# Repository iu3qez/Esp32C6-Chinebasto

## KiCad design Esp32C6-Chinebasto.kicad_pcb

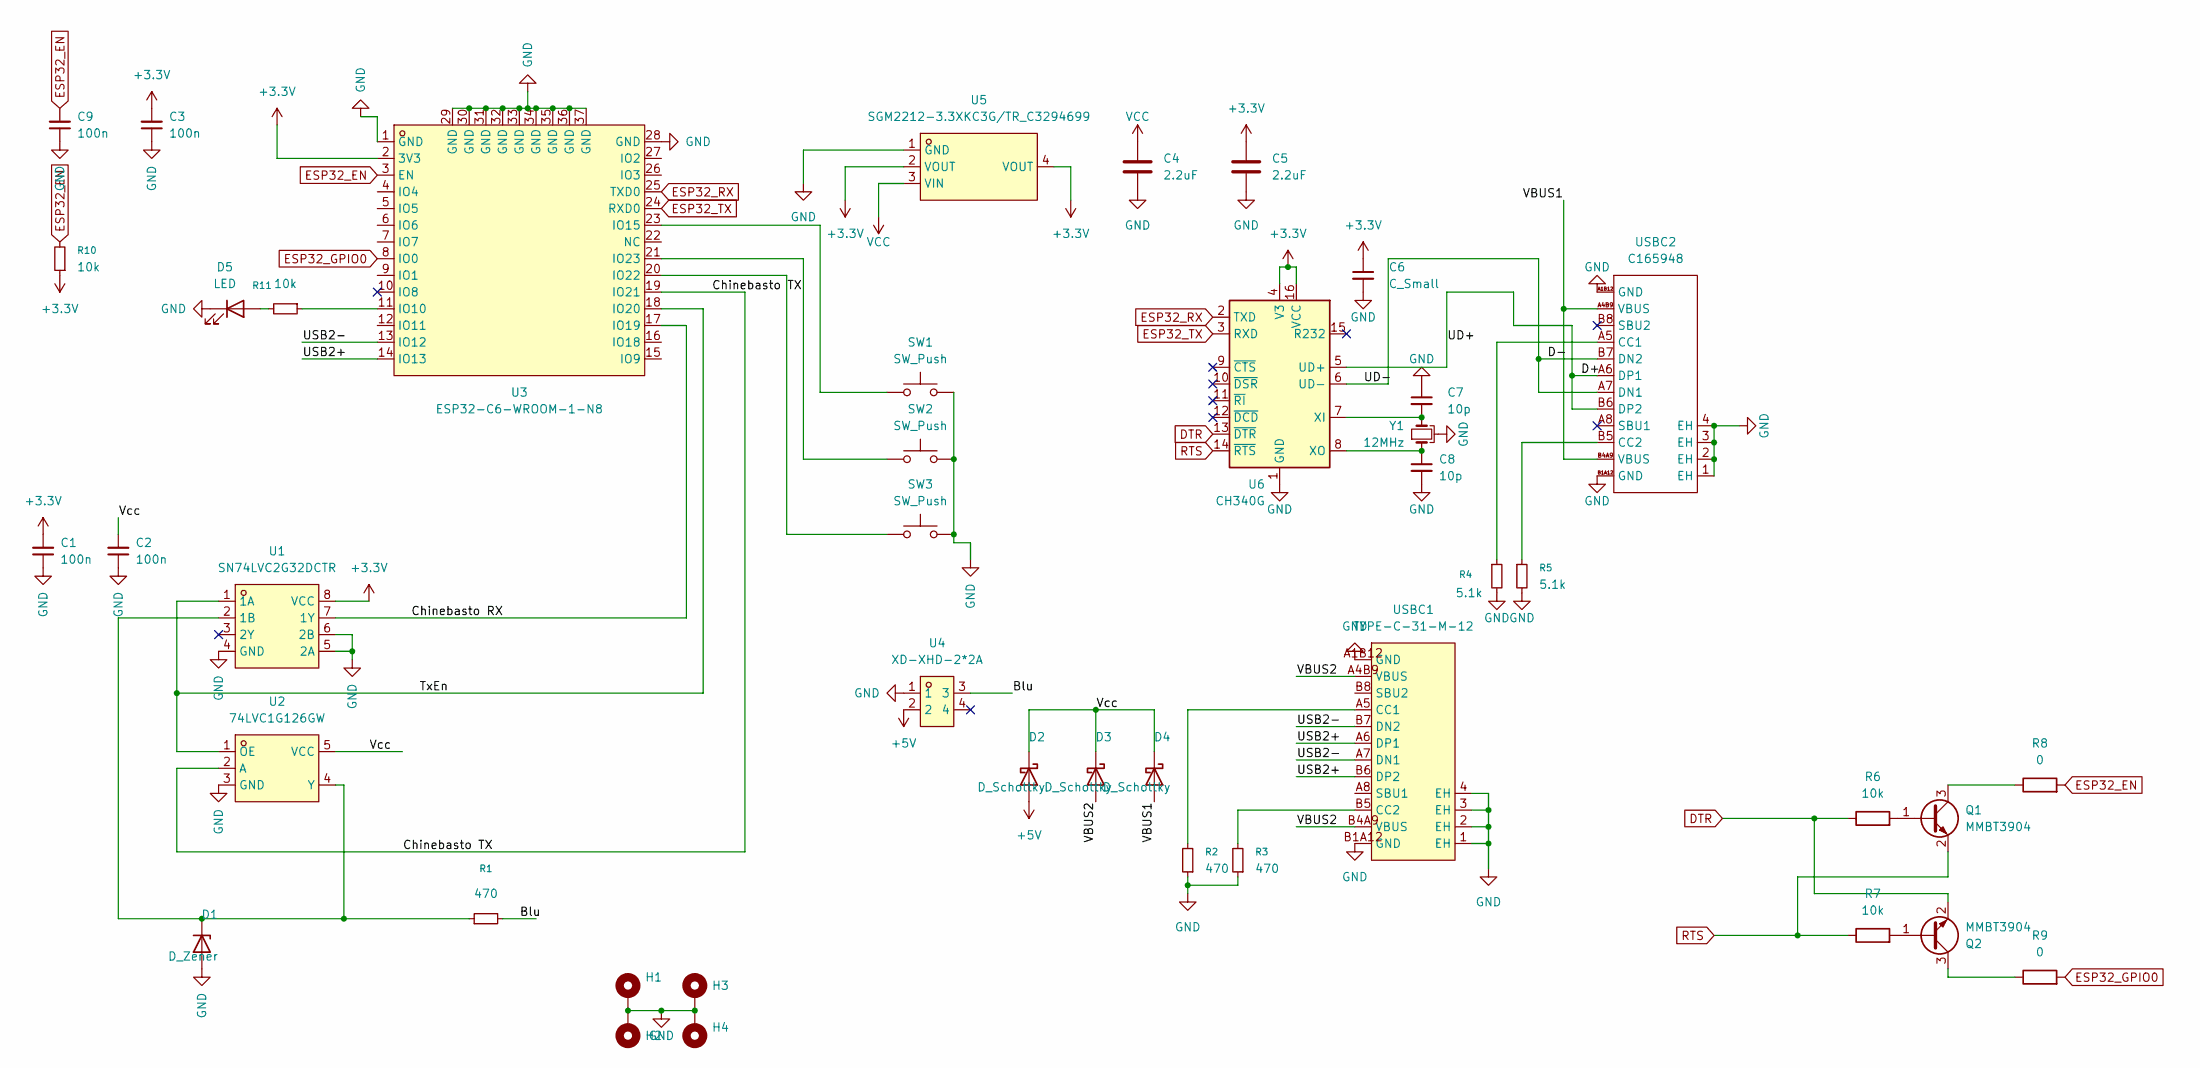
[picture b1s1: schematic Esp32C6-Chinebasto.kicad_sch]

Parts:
C1, C2, C3, C9: 100n; C_0603_1608Metric_Pad1.08x0.95mm_HandSolder
C4, C5: 2.2uF; C_0805_2012Metric_Pad1.18x1.45mm_HandSolder
C6: C_Small; C_0603_1608Metric_Pad1.08x0.95mm_HandSolder
C7, C8: 10p; C_0603_1608Metric_Pad1.08x0.95mm_HandSolder
D1: D_Zener; D_MiniMELF
D2, D3, D4: D_Schottky; D_SOD-123
D5: LED; LED_0603_1608Metric_Pad1.05x0.95mm_HandSolder
H1, H2, H3, H4: MountingHole_Pad; MountingHole_3.2mm_M3_ISO7380_Pad_TopBottom
Q1, Q2: MMBT3904; SOT-23
R1, R2, R3: 470; R_0603_1608Metric_Pad0.98x0.95mm_HandSolder
R4, R5: 5.1k; R_0603_1608Metric_Pad0.98x0.95mm_HandSolder
R6, R7, R10, R11: 10k; R_0603_1608Metric_Pad0.98x0.95mm_HandSolder
R8, R9: 0; R_0603_1608Metric_Pad0.98x0.95mm_HandSolder
SW1, SW2, SW3: SW_Push; SW_Kailh_Choc_V1V2_1.00u
U1: SN74LVC2G32DCTR; SM-8_L3.0-W2.8-P0.65-LS4.0-BL; LCSC Part C2862085
U2: 74LVC1G126GW; SOT-353-5_L2.0-W1.6-P0.65-LS2.1-BL; LCSC Part C52140429
U3: ESP32-C6-WROOM-1-N8; WIRELM-SMD_ESP32-C6-WROOM-1; LCSC Part C5366877
U4: XD-XHD-2*2A; CONN-TH_XD-XHD-2-2A; LCSC Part C17700790
U5: SGM2212-3.3XKC3G/TR_C3294699; SOT-223-3_L6.5-W3.4-P2.30-LS7.0-BR; LCSC Part C3294699
U6: CH340G; SOIC-16_L9.9-W3.9-P1.27-LS6.0-BL
USBC1: TYPE-C-31-M-12; USB-C_SMD-TYPE-C-31-M-12_1; LCSC Part C165948
USBC2: C165948; USB-C_SMD-TYPE-C-31-M-12_1; Manufacturer Part TYPE-C-31-M-12; LCSC Part Name Type-C 母 卧贴
Y1: 12MHz; CRYSTAL-SMD_4P-L3.2-W2.5-BL

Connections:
+3.3V: C1.2, C3.2, C5.1, C6.1, R10.1, U1.8 (VCC), U3.2 (3V3), U5.2 (VOUT), U5.4 (VOUT), U6.4 (V3), U6.16 (VCC)
+5V: D2.2 (A), U4.2
/Blu: R1.2, U4.3
/Chinebasto RX: U1.7 (1Y), U3.17 (IO19)
/Chinebasto TX: U2.2 (A), U3.19 (IO21)
/D+: U6.5 (UD+), USBC2.A6 (DP1), USBC2.B6 (DP2)
/D-: U6.6 (UD-), USBC2.A7 (DN1), USBC2.B7 (DN2)
/TxEn: U1.1 (1A), U2.1 (OE), U3.18 (IO20)
/USB2+: U3.14 (IO13), USBC1.A6 (DP1), USBC1.B6 (DP2)
/USB2-: U3.13 (IO12), USBC1.A7 (DN1), USBC1.B7 (DN2)
/VBUS1: D4.2 (A), USBC2.A4B9 (VBUS), USBC2.B4A9 (VBUS)
/VBUS2: D3.2 (A), USBC1.A4B9 (VBUS), USBC1.B4A9 (VBUS)
/Vcc: C2.2, D2.1 (K), D3.1 (K), D4.1 (K), U2.5 (VCC)
DTR: Q2.2 (E), R6.1, U6.13 (~DTR)
ESP32_EN: C9.2, R8.2, R10.2, U3.3 (EN)
ESP32_GPIO0: R9.2, U3.8 (IO0)
ESP32_RX: U3.25 (TXD0), U6.2 (TXD)
ESP32_TX: U3.24 (RXD0), U6.3 (RXD)
GND: C1.1, C2.1, C3.1, C4.2, C5.2, C6.2, C7.1, C8.2, C9.1, D1.2 (A), D5.1 (K), H1.1 (1_1), H2.1 (1_1), H3.1 (1_1), H4.1 (1_1), R2.1, R3.1, R4.2, R5.2, SW1.2, SW2.2, SW3.2, U1.4 (GND), U1.5 (2A), U1.6 (2B), U2.3 (GND), U3.1 (GND), U3.28 (GND), U3.29 (GND), U3.30 (GND), U3.31 (GND), U3.32 (GND), U3.33 (GND), U3.34 (GND), U3.35 (GND), U3.36 (GND), U3.37 (GND), U4.1, U5.1 (GND), U6.1 (GND), USBC1.1 (EH), USBC1.2 (EH), USBC1.3 (EH), USBC1.4 (EH), USBC1.A1B12 (GND), USBC1.B1A12 (GND), USBC2.1 (EH), USBC2.2 (EH), USBC2.3 (EH), USBC2.4 (EH), USBC2.A1B12 (GND), USBC2.B1A12 (GND), Y1.2, Y1.4
unnamed: D1.1 (K), R1.1, U1.2 (1B), U2.4 (Y)
unnamed: D5.2 (A), R11.2
unnamed: Q1.1 (B), R6.2
unnamed: Q1.3 (C), R8.1
unnamed: Q2.1 (B), R7.2
unnamed: Q2.3 (C), R9.1
unnamed: R11.1, U3.11 (IO10)
unnamed: SW1.1, U3.23 (IO15)
unnamed: SW3.1, U3.20 (IO22)
unnamed: SW2.1, U3.21 (IO23)
unnamed: C7.2, U6.7 (XI), Y1.3
unnamed: C8.1, U6.8 (XO), Y1.1
unnamed: R2.2, USBC1.A5 (CC1)
unnamed: R3.2, USBC1.B5 (CC2)
unnamed: R4.1, USBC2.A5 (CC1)
unnamed: R5.1, USBC2.B5 (CC2)
RTS: Q1.2 (E), R7.1, U6.14 (~RTS)
VCC: C4.1, U5.3 (VIN)

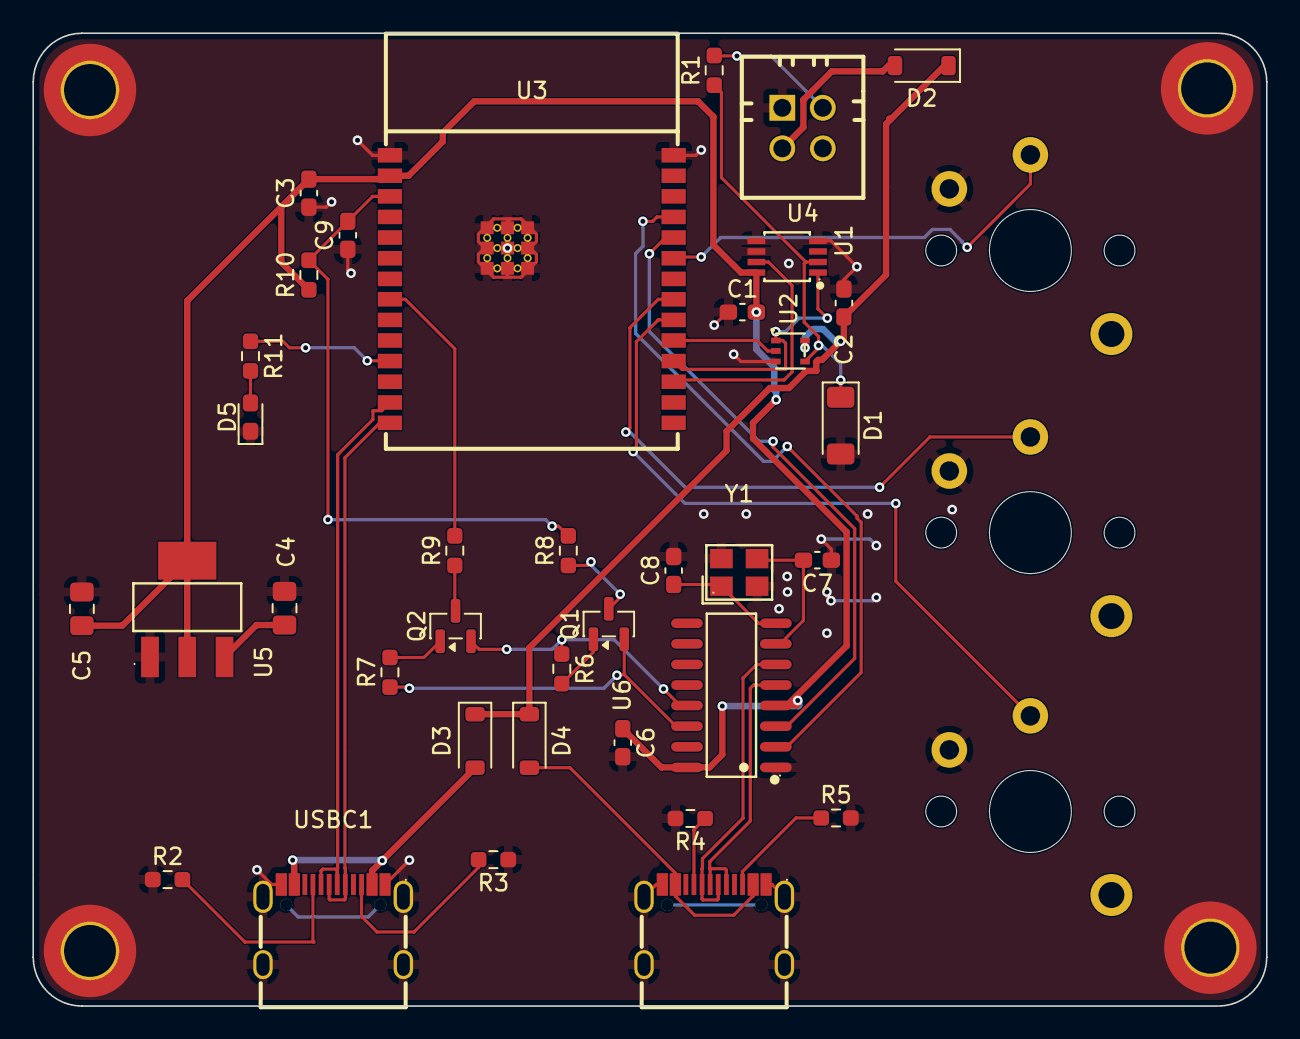
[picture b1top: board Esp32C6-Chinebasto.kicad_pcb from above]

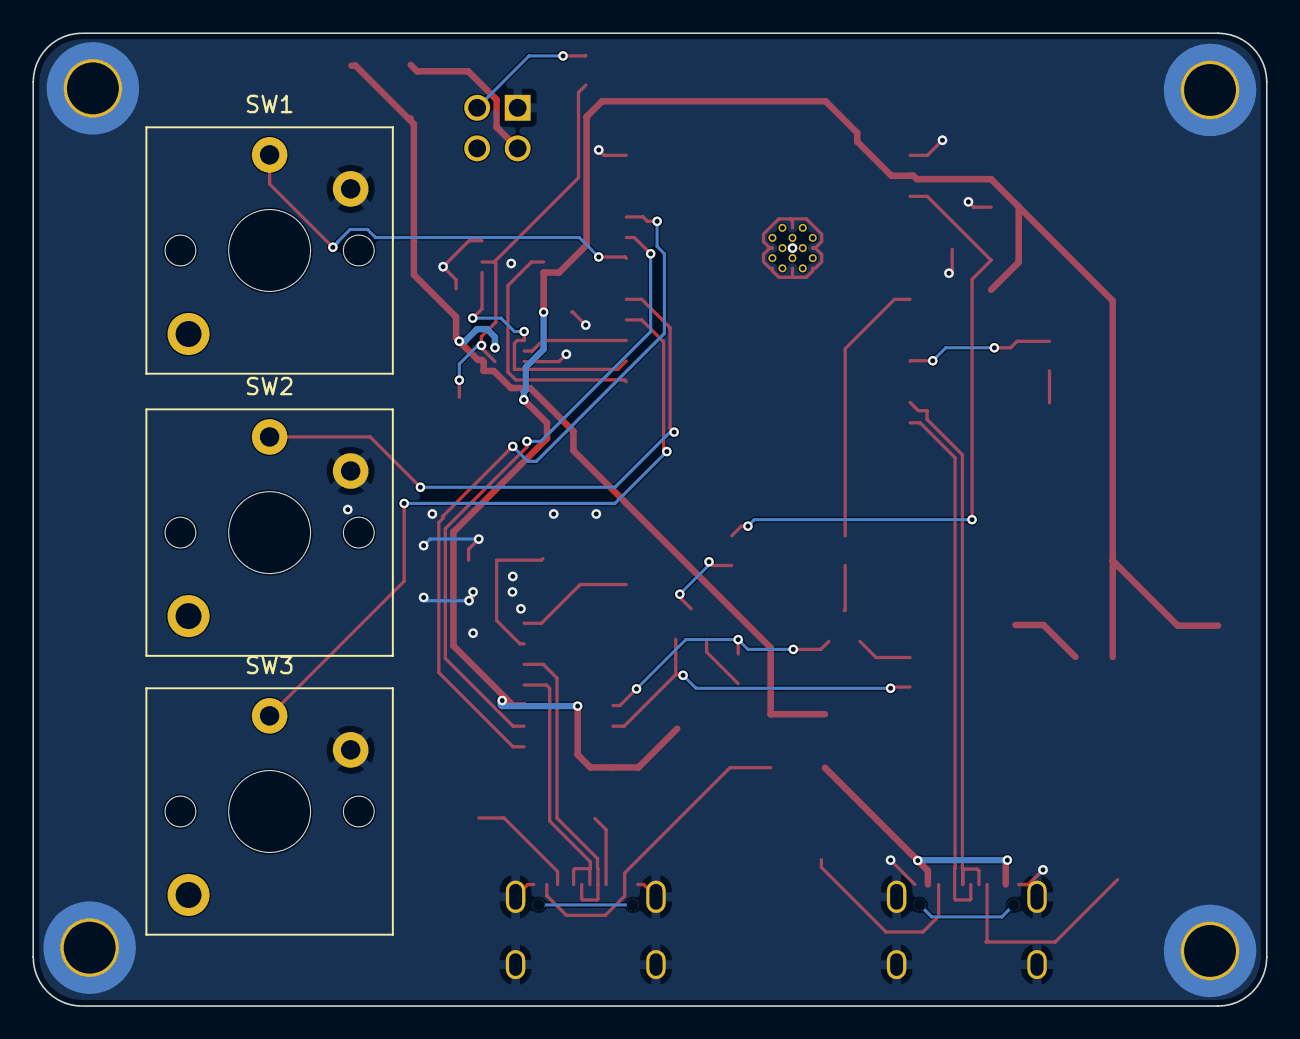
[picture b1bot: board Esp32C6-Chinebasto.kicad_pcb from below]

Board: 2 copper layers, 76.1 x 60.0 mm, 43 parts (3 on the bottom side), 37 nets.

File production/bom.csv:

Designator,Footprint,Quantity,Value,LCSC Part #
"C1, C2, C3, C9",0603,4,100n,
"C4, C5",0805,2,2.2uF,
C6,0603,1,C_Small,
"C7, C8",0603,2,10p,
D1,D_MiniMELF,1,D_Zener,
"D2, D3, D4",D_SOD-123,3,D_Schottky,
D5,0603,1,LED,
"Q1, Q2",SOT-23,2,MMBT3904,
"R1, R2, R3",0603,3,470,
"R10, R11, R6, R7",0603,4,10k,
"R4, R5",0603,2,5.1k,
"R8, R9",0603,2,0,
"SW1, SW2, SW3",SW_Kailh_Choc_V1V2_1.00u,3,SW_Push,
U1,SM-8_L3.0-W2.8-P0.65-LS4.0-BL,1,SN74LVC2G32DCTR,C2862085
U2,SOT-353-5_L2.0-W1.6-P0.65-LS2.1-BL,1,74LVC1G126GW,C52140429
U3,WIRELM-SMD_ESP32-C6-WROOM-1,1,ESP32-C6-WROOM-1-N8,C5366877
U4,CONN-TH_XD-XHD-2-2A,1,XD-XHD-2*2A,C17700790
U5,SOT-223-3_L6.5-W3.4-P2.30-LS7.0-BR,1,SGM2212-3.3XKC3G/TR_C3294699,C3294699
U6,SOIC-16_L9.9-W3.9-P1.27-LS6.0-BL,1,CH340G,
USBC1,USB-C_SMD-TYPE-C-31-M-12_1,1,TYPE-C-31-M-12,C165948
USBC2,USB-C_SMD-TYPE-C-31-M-12_1,1,C165948,
Y1,CRYSTAL-SMD_4P-L3.2-W2.5-BL,1,12MHz,

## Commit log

2026-02-22 Normalize line endings
2026-02-22 feat: add .gitignore file to exclude VS Code and KiCad temporary files
    Add .gitignore configuration to prevent tracking of VS Code local history files and KiCad backup/autosave files. This improves repository cleanliness by excluding generated and temporary files that s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
2026-02-22 updated .gitignore
2026-02-22 just started
2026-02-23 updatee
2026-02-26 Production Files
